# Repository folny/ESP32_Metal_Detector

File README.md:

# ESP32 Metal Detector

BLE Library https://github.com/nkolban/ESP32_BLE_Arduino

Forum http://www.geotech1.com/forums/showthread.php?24589-ESP32-Metal-detector

https://www.youtube.com/watch?v=ikg0VJCtUzE

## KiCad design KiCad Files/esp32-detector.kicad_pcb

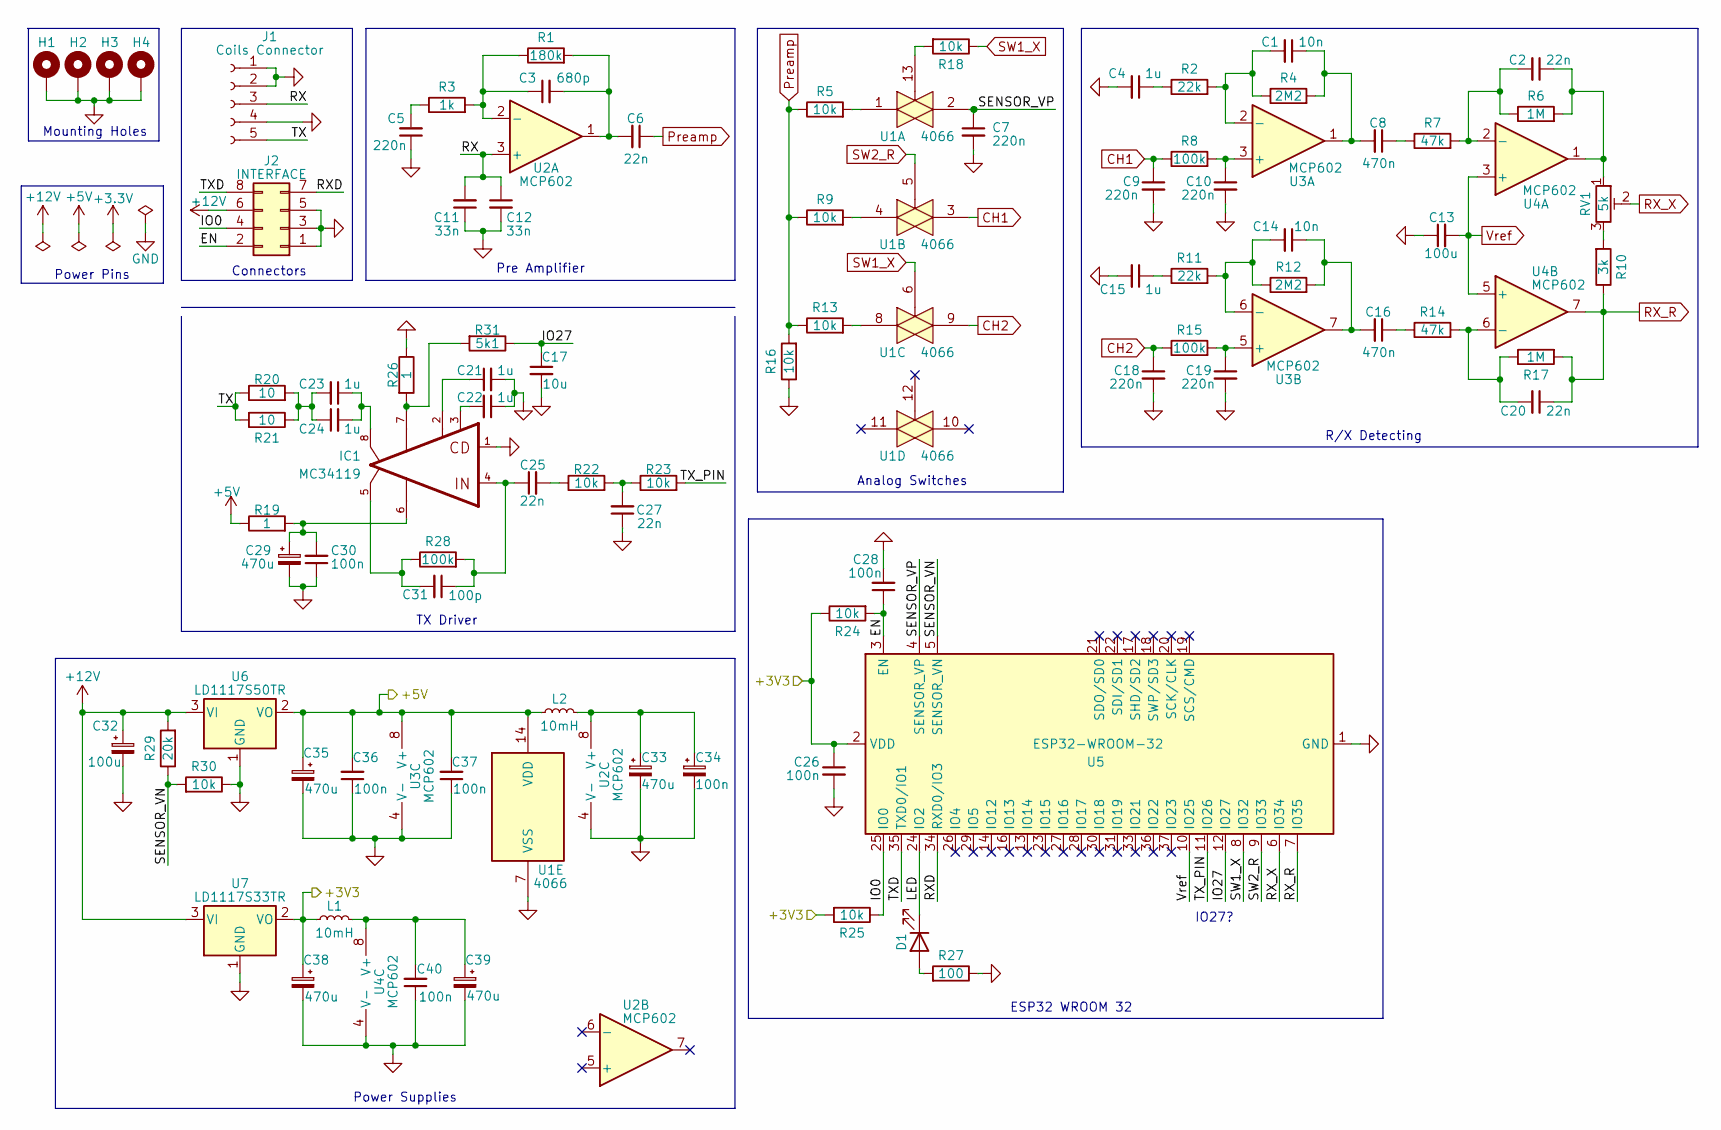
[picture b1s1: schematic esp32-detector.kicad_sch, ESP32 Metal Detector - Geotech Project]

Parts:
C1, C14: 10n; C_1206_3216Metric_Pad1.33x1.80mm_HandSolder
C2, C6, C20, C25, C27: 22n; C_1206_3216Metric_Pad1.33x1.80mm_HandSolder
C3: 680p; C_1206_3216Metric_Pad1.33x1.80mm_HandSolder
C4, C15, C21, C22, C23, C24: 1u; C_1206_3216Metric_Pad1.33x1.80mm_HandSolder
C5, C7, C9, C10, C18, C19: 220n; C_1206_3216Metric_Pad1.33x1.80mm_HandSolder
C8, C16: 470n; C_1206_3216Metric_Pad1.33x1.80mm_HandSolder
C11, C12: 33n; C_1206_3216Metric_Pad1.33x1.80mm_HandSolder
C13: 100u; C_1206_3216Metric_Pad1.33x1.80mm_HandSolder
C17: 10u; C_1206_3216Metric_Pad1.33x1.80mm_HandSolder
C26, C28, C30, C34, C36, C37, C40: 100n; C_1206_3216Metric_Pad1.33x1.80mm_HandSolder
C29, C33, C38, C39: 470u; C_1812_4532Metric_Pad1.57x3.40mm_HandSolder
C31: 100p; C_1206_3216Metric_Pad1.33x1.80mm_HandSolder
C32: 100u; C_2220_5650Metric_Pad1.97x5.40mm_HandSolder
C35: 470u; C_2220_5650Metric_Pad1.97x5.40mm_HandSolder
D1: LED; LED_1206_3216Metric_Pad1.42x1.75mm_HandSolder
H1, H2, H3, H4: MountingHole_Pad; MountingHole_3mm_Pad_Via
IC1: MC34119; TSSOP-8_4.4x3mm_P0.65mm
J1: Coils Connector; SolderWire-0.1sqmm_1x05_P3.6mm_D0.4mm_OD1mm
J2: INTERFACE; Hirose_DF11-8DP-2DSA_2x04_P2.00mm_Vertical
L1: 10mH; L_1812_4532Metric_Pad1.30x3.40mm_HandSolder
L2: 10mH; L_Taiyo-Yuden_NR-60xx_HandSoldering
R1: 180k; R_1206_3216Metric_Pad1.30x1.75mm_HandSolder
R2, R11: 22k; R_1206_3216Metric_Pad1.30x1.75mm_HandSolder
R3: 1k; R_1206_3216Metric_Pad1.30x1.75mm_HandSolder
R4, R12: 2M2; R_1206_3216Metric_Pad1.30x1.75mm_HandSolder
R5, R9, R13, R16, R18, R22, R23, R24, R25, R30: 10k; R_1206_3216Metric_Pad1.30x1.75mm_HandSolder
R6, R17: 1M; R_1206_3216Metric_Pad1.30x1.75mm_HandSolder
R7, R14: 47k; R_1206_3216Metric_Pad1.30x1.75mm_HandSolder
R8, R15, R28: 100k; R_1206_3216Metric_Pad1.30x1.75mm_HandSolder
R10: 3k; R_1206_3216Metric_Pad1.30x1.75mm_HandSolder
R19, R26: 1; R_1206_3216Metric_Pad1.30x1.75mm_HandSolder
R20, R21: 10; R_1206_3216Metric_Pad1.30x1.75mm_HandSolder
R27: 100; R_1206_3216Metric_Pad1.30x1.75mm_HandSolder
R29: 20k; R_1206_3216Metric_Pad1.30x1.75mm_HandSolder
R31: 5k1; R_1206_3216Metric_Pad1.30x1.75mm_HandSolder
RV1: 5k; Potentiometer_Vishay_TS53YL_Vertical
U1: 4066; SO-14_3.9x8.65mm_P1.27mm
U2: MCP602
U3, U4: MCP602; SOIC-8_3.9x4.9mm_P1.27mm
U5: ESP32-WROOM-32
U6: LD1117S50TR; SOT-223-3_TabPin2
U7: LD1117S33TR; SOT-223-3_TabPin2

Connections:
+5V: C35.1, C36.2, C37.2, L2.1, R19.1, U1.14 (VDD), U3.8 (V+), U6.2 (VO)
+12V: C32.1, J2.6, R29.2, U6.3 (VI), U7.3 (VI)
/+3V3: C26.1, C38.1, L1.1, R24.1, R25.2, U5.2 (VDD), U7.2 (VO)
/EN: C28.1, J2.2, R24.2, U5.3 (EN)
/IO0: J2.4, R25.1, U5.25 (IO0)
/IO27: C17.1, R31.1, U5.12 (IO27)
/LED: D1.1 (K), U5.24 (IO2)
/RX: C11.2, C12.1, J1.3, U2.3 (+)
/RXD: J2.7, U5.34 (RXD0/IO3)
/SENSOR_VN: R29.1, R30.2, U5.5 (SENSOR_VN)
/SENSOR_VP: U5.4 (SENSOR_VP)
/TX: J1.5, R20.1, R21.2
/TXD: J2.8, U5.35 (TXD0/IO1)
/TX_PIN: R23.2, U5.11 (IO26)
CH1: C9.1, R8.1, U1.3
CH2: C18.1, R15.1, U1.9
GND: C4.2, C5.1, C7.2, C9.2, C10.2, C11.1, C12.2, C13.1, C15.2, C17.2, C18.2, C19.2, C21.2, C22.1, C26.2, C27.1, C28.2, C29.2, C30.1, C32.2, C33.2, C34.2, C35.2, C36.1, C37.1, C38.2, C39.2, C40.1, H1.1, H2.1, H3.1, H4.1, IC1.1, J1.1, J1.2, J1.4, J2.1, J2.3, J2.5, R16.1, R26.1, R27.1, R30.1, U1.7 (VSS), U2.4 (V-), U3.4 (V-), U4.4 (V-), U5.1 (GND), U5.15 (GND), U5.38 (GND), U5.39 (GND), U6.1 (GND), U7.1 (GND)
unnamed: C1.1, C8.2, R4.2, U3.1
unnamed: C1.2, R2.2, R4.1, U3.2 (-)
unnamed: C2.1, R6.2, RV1.1, U4.1
unnamed: C2.2, R6.1, R7.2, U4.2 (-)
unnamed: C3.1, R1.1, R3.2, U2.2 (-)
unnamed: C3.2, C6.2, R1.2, U2.1
unnamed: C4.1, R2.1
unnamed: C5.2, R3.1
unnamed: C7.1, U1.2
unnamed: C8.1, R7.1
unnamed: C10.1, R8.2, U3.3 (+)
unnamed: C14.1, C16.2, R12.2, U3.7
unnamed: C14.2, R11.2, R12.1, U3.6 (-)
unnamed: C15.1, R11.1
unnamed: C16.1, R14.1
unnamed: C19.1, R15.2, U3.5 (+)
unnamed: C20.2, R14.2, R17.1, U4.6 (-)
unnamed: C21.1, IC1.2
unnamed: C22.2, IC1.3
unnamed: C23.1, C24.2, IC1.8
unnamed: C23.2, C24.1, R20.2, R21.1
unnamed: C25.1, C31.1, IC1.4, R28.2
unnamed: C25.2, R22.1
unnamed: C27.2, R22.2, R23.1
unnamed: C29.1, C30.2, IC1.6, R19.2
unnamed: C31.2, IC1.5, R28.1
unnamed: C33.1, C34.1, L2.2, U2.8 (V+)
unnamed: C39.1, C40.2, L1.2, U4.8 (V+)
unnamed: D1.2 (A), R27.2
unnamed: IC1.7, R26.2, R31.2
unnamed: R5.2, U1.1
unnamed: R9.2, U1.4
unnamed: R10.2, RV1.3
unnamed: R13.2, U1.8
unnamed: R18.2, U1.13
Preamp: C6.1, R5.1, R9.1, R13.1, R16.2
RX_R: C20.1, R10.1, R17.2, U4.7, U5.7 (IO35)
RX_X: RV1.2, U5.6 (IO34)
SW1_X: R18.1, U1.6, U5.8 (IO32)
SW2_R: U1.5, U5.9 (IO33)
Vref: C13.2, U4.3 (+), U4.5 (+), U5.10 (IO25)

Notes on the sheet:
IO27?
Connectors
R/X Detecting
Analog Switches
Mounting Holes
TX Driver
Power Pins
Power Supplies
Pre Amplifier
ESP32 WROOM 32

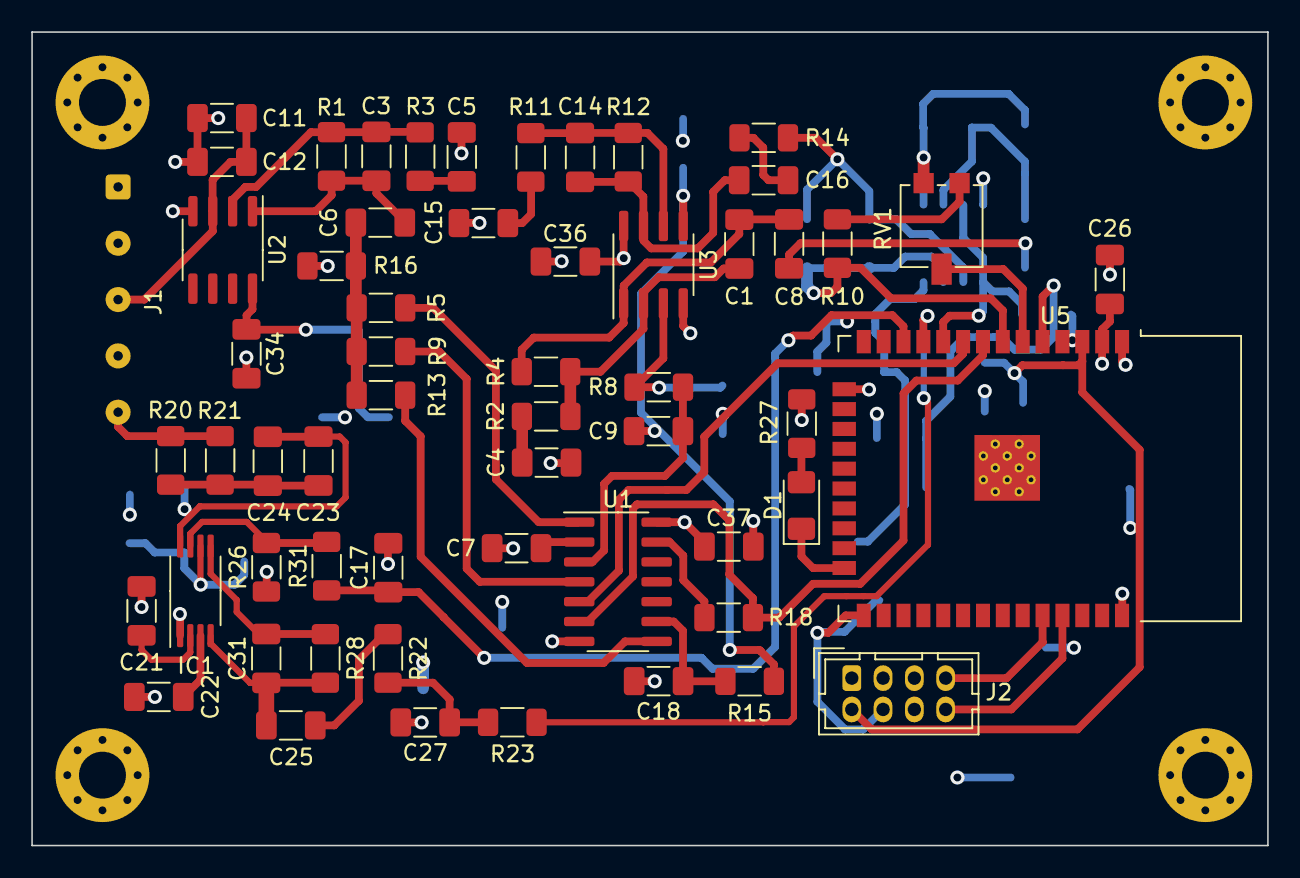
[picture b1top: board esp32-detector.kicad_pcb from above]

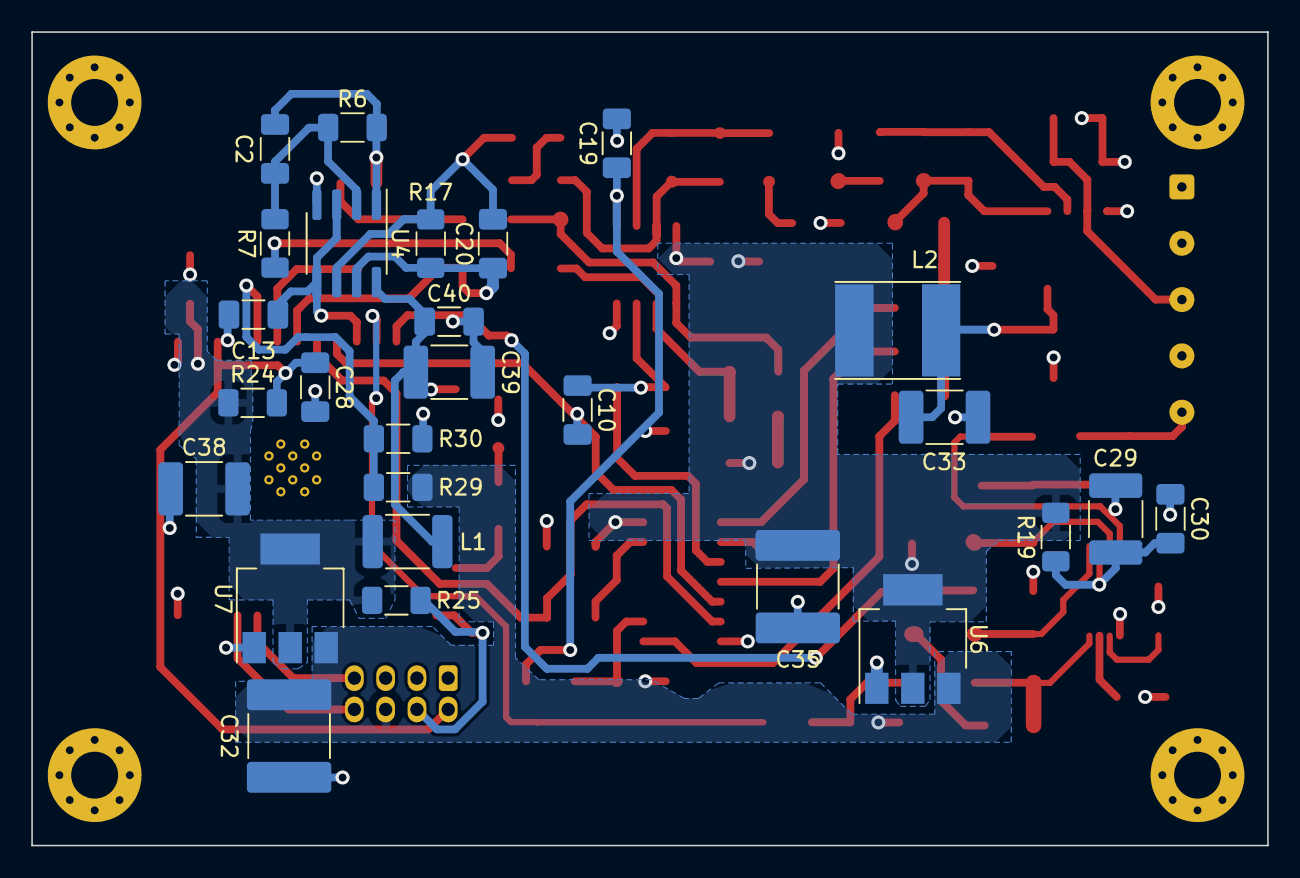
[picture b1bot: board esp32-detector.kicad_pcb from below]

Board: 4 copper layers, 79.0 x 52.0 mm, 89 parts (27 on the bottom side), 57 nets.

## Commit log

2022-12-15 Upload KiCad Files
2022-12-16 Upload Schematic and PCB files
2022-12-16 Add BOM file
2022-12-20 Via improvement
